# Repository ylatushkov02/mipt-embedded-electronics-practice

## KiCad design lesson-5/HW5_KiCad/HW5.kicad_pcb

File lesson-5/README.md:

# ДЗ № 5. Датчик протечки

## Задание
Нужно собрать датчик протечки со звуковой и световой индикацией:
- электроды — соединительные провода, испытание в стакане с водой;
- питание 5 В;
- сначала отладка на макетной плате, потом сборка на монтажной плате пайкой;
- электроды подключаются через винтовой клеммник.

Кроме того, нужны принципиальная схема в KiCad, разводка печатной платы, чертежи в PDF и скриншоты 3D-вида сверху и снизу.

## Схема
Ключ на одном NPN-транзисторе BC547B, включённом по схеме с общим эмиттером.
- Пока электроды сухие, R2 (100 кОм) держит базу на GND, и транзистор закрыт.
- Когда электроды в воде, ток течёт по цепи +5 В → вода → R1 (1 кОм) → база. Q1 открывается и одновременно включает:
  - активный зуммер TMB12A05;
  - светодиод D1 через R3 (220 Ом).

Расчёт:
- I_к ≈ 30 + 13 = 43 мА, это меньше 100 мА;
- I_б min ≈ 0,22 мА, поэтому сопротивление воды должно быть не больше ≈ 18 кОм;
- если электроды замкнуть накоротко, R1 ограничит ток базы до 4,3 мА.

## Файлы
| Файл | Что это |
|---|---|
| `HW5_KiCad/HW5.kicad_sch` | Принципиальная схема с расчётом, рамка ГОСТ (`GOST_A4.kicad_wks`) |
| `HW5_KiCad/HW5.kicad_pcb` | Печатная плата 60 × 35 мм: дорожки на B.Cu, винтовые клеммники J1 (питание) и J2 (электроды), размеры на User.Drawings, пояснения на User.Comments |
| `Схема_ДЗ5_предпросмотр.pdf` | Предпросмотр схемы |
| `Плата_ДЗ5_трассировка_предпросмотр.pdf` | Предпросмотр платы: трассировка и сборочный чертёж |
| `Монтажная_плата_схема_пайки.png` | Расположение элементов и перемычек на монтажной плате (шаг 2,54 мм) |
| `Макетка_датчик_протечки.png` | Сборка на макетной плате |
| `Видео_датчик_протечки_макетка.mov` | Испытание в стакане с водой (макетная плата) |

## Цепи
| Цепь | Выводы |
|---|---|
| +5V | J1.1, J2.2, BZ1.+, R3.1 |
| GND | J1.2, Q1.E, R2.2 |
| SENSE | J2.1, R1.1 |
| BASE | R1.2, R2.1, Q1.B |
| LOAD | Q1.C, BZ1.−, D1.K |
| LED_A | R3.2, D1.A |

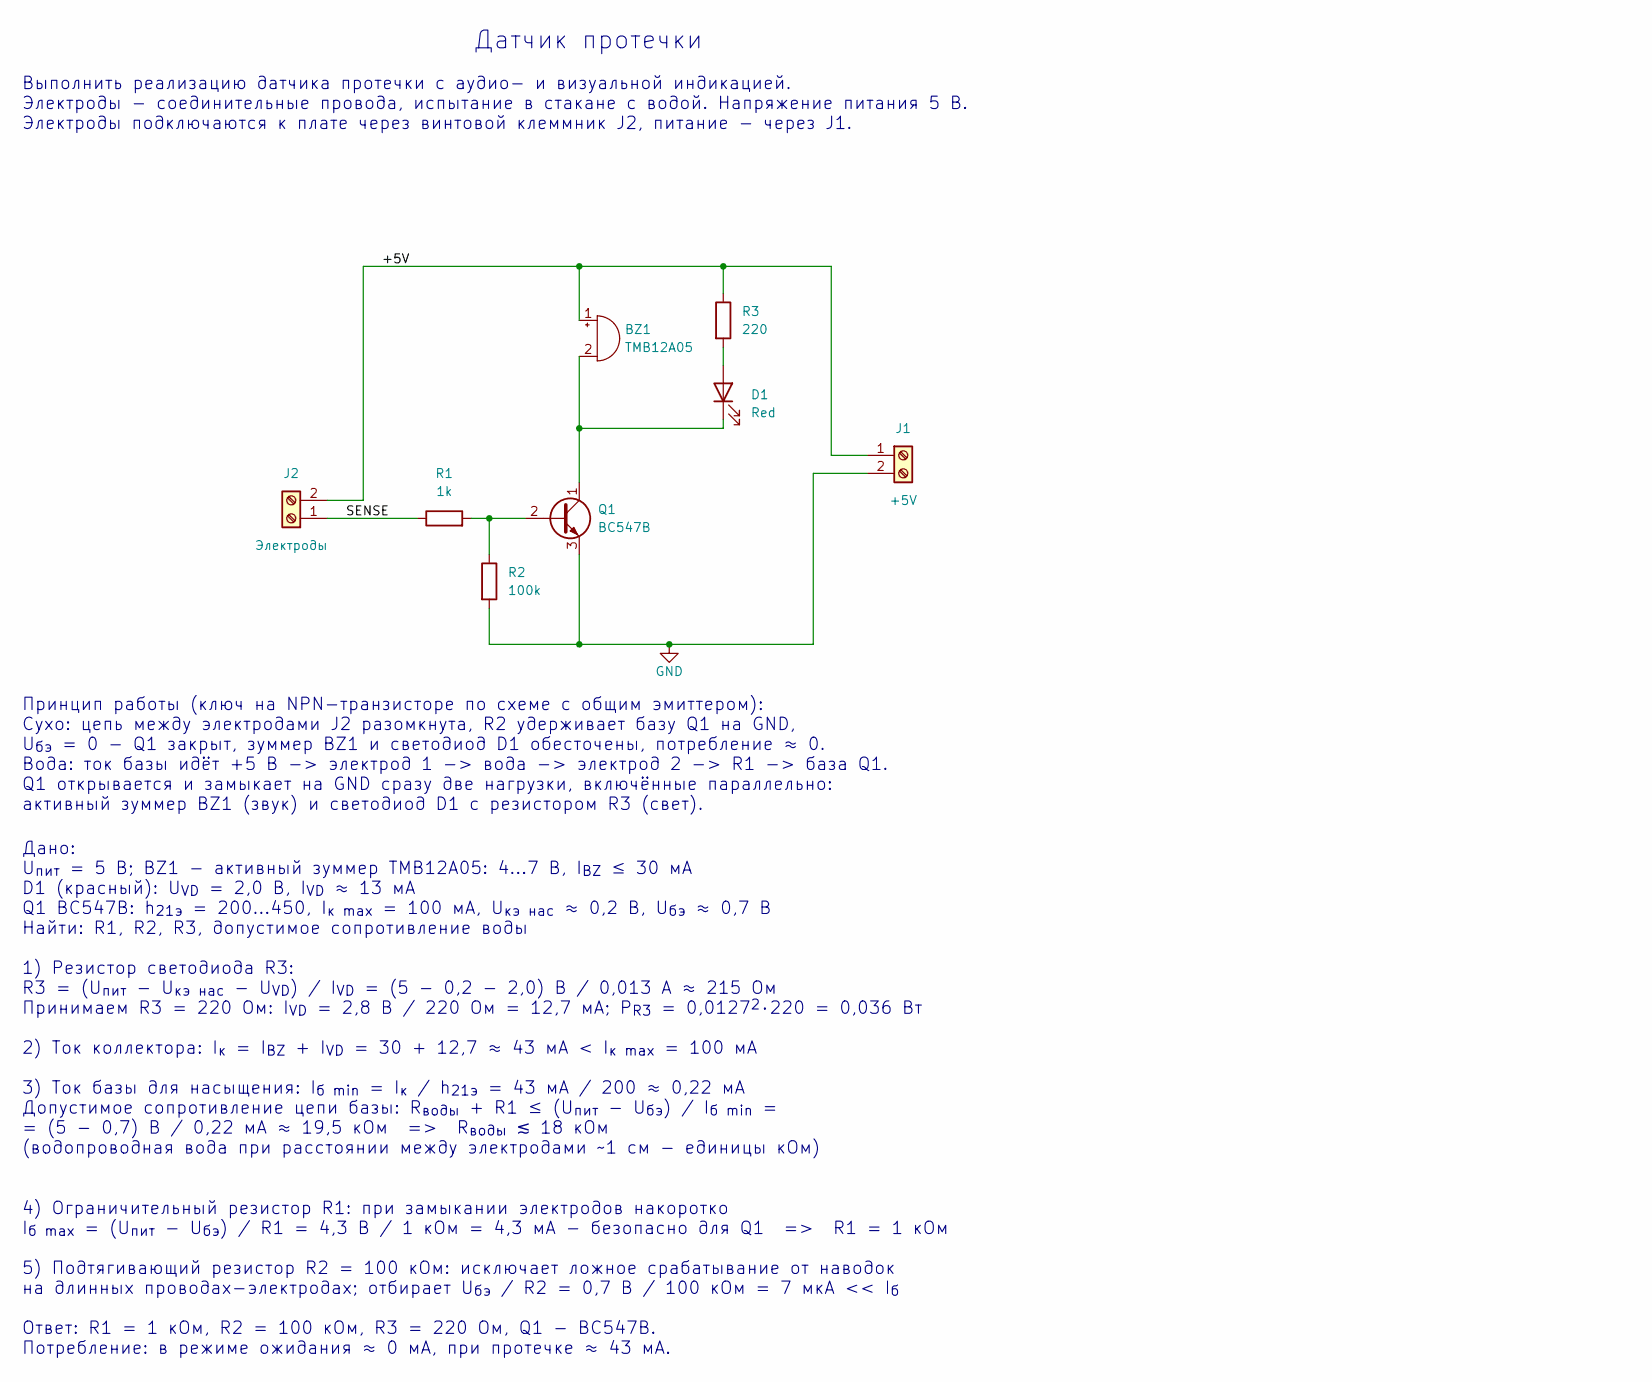
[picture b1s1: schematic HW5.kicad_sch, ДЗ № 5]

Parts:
BZ1: TMB12A05; Buzzer_12x9.5RM7.6
D1: Red; LED_D5.0mm
J1: +5V; TerminalBlock_MaiXu_MX126-5.0-02P_1x02_P5.00mm
J2: Электроды; TerminalBlock_MaiXu_MX126-5.0-02P_1x02_P5.00mm
Q1: BC547B; TO-92L_Inline
R1: 1k; R_Axial_DIN0207_L6.3mm_D2.5mm_P10.16mm_Horizontal
R2: 100k; R_Axial_DIN0207_L6.3mm_D2.5mm_P10.16mm_Horizontal
R3: 220; R_Axial_DIN0207_L6.3mm_D2.5mm_P10.16mm_Horizontal

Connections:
+5V: BZ1.1 (+), J1.1, J2.2, R3.1
BASE: Q1.2 (B), R1.2, R2.1
GND: J1.2, Q1.3 (E), R2.2
LED_A: D1.2 (A), R3.2
LOAD: BZ1.2 (-), D1.1 (K), Q1.1 (C)
SENSE: J2.1, R1.1

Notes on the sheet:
Датчик протечки
Выполнить реализацию датчика протечки с аудио- и визуальной индикацией. Электроды - соединительные провода, испытание в стакане с водой. Напряжение питания 5 В. Электроды подключаются к плате через винтовой клеммник J2, питание - через J1.
Принцип работы (ключ на NPN-транзисторе по схеме с общим эмиттером): Сухо: цепь между электродами J2 разомкнута, R2 удерживает базу Q1 на GND, U_{бэ} = 0 - Q1 закрыт, зуммер BZ1 и светодиод D1 обесточены, потребление ≈ 0. Вода: ток базы идёт +5 В -> электрод 1 -> вода -> электрод 2 -> R1 -> база Q1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
Дано: U_{пит} = 5 В; BZ1 - активный зуммер TMB12A05: 4...7 В, I_{BZ} ≤ 30 мА D1 (красный): U_{VD} = 2,0 В, I_{VD} ≈ 13 мА Q1 BC547B: h_{21э} = 200...450, I_{к max} = 100 мА, U_{кэ нас} ≈ 0,2 В, U_{бэ} ≈ 0,7 В Найти: R1, R2, R3, допустимое сопротивление воды 1) Резистор светодиода R3: R3 = (U_{пит} 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
4) Ограничительный резистор R1: при замыкании электродов накоротко I_{б max} = (U_{пит} - U_{бэ}) / R1 = 4,3 В / 1 кОм = 4,3 мА - безопасно для Q1 => R1 = 1 кОм 5) Подтягивающий резистор R2 = 100 кОм: исключает ложное срабатывание от наводок на длинных проводах-электродах; отбирает U_{бэ} / R2 = 0,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

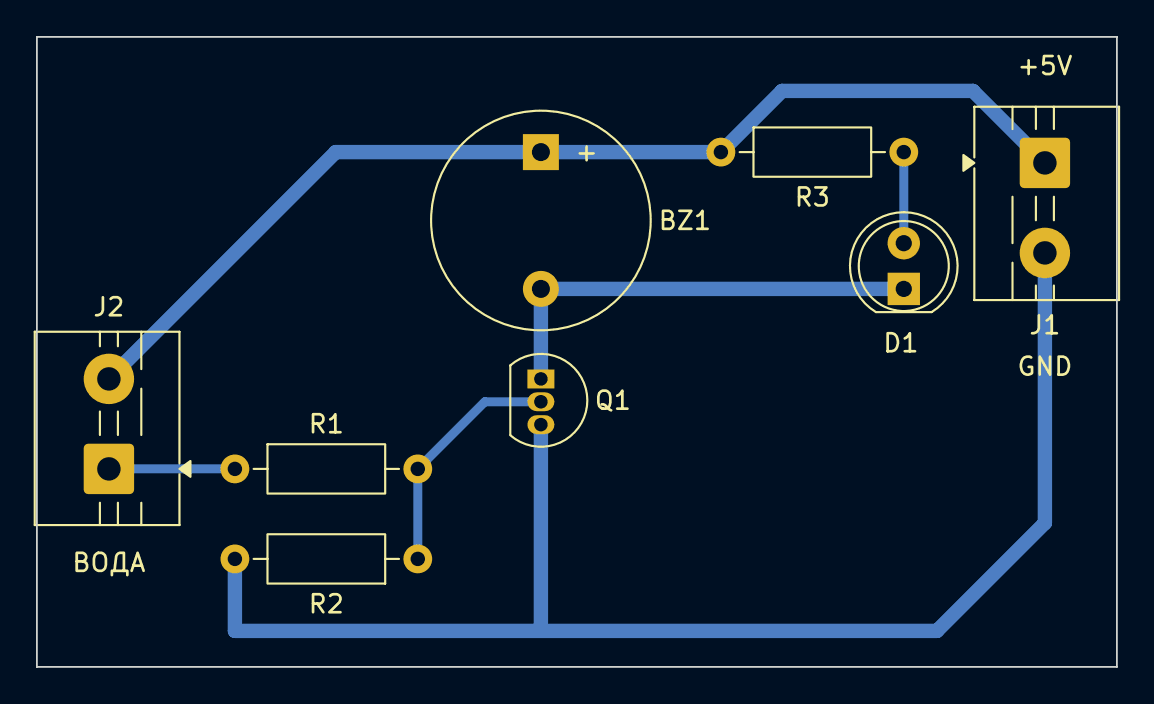
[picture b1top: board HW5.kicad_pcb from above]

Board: 2 copper layers, 60.0 x 35.0 mm, 8 parts (0 on the bottom side), 6 nets.

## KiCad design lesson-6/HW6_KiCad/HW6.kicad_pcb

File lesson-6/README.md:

# ДЗ № 6. Параметрический стабилизатор 12 В → 5 В

## Задание
Собрать на макетной плате параметрический стабилизатор: вход 12 В, выход 5 В.

Нагрузка — пять параллельных светодиодов:
- красный;
- жёлтый;
- зелёный;
- синий;
- белый.

В каждой ветви стоит свой резистор. Нужно рассчитать ток делителя со стабилитроном с учётом тока базы транзистора и запасом 30 %. Схему выполнить в KiCad. Дополнительно (задание со звёздочкой): развести плату.

Лампы накаливания в наборе нет, поэтому нагрузка состоит только из светодиодов.

## Схема
- Стабилитрон D1 BZX55C6V2 питается от 12 В через R1 = 1 кОм. Он задаёт опорное напряжение 6,2 В на базе Q1.
- Q1 (BC547B) включён эмиттерным повторителем, поэтому на выходе U = U_ст − U_бэ ≈ 6,2 − 0,75 = 5,45 В.
- R2 = 47 Ом в цепи коллектора забирает часть напряжения, поэтому транзистор греется меньше: 0,21 Вт вместо 0,34 Вт.

## Расчёт
- Резисторы светодиодов:
  - красный, жёлтый, зелёный (2,1 В): (5,45 − 2,1) / 10 мА ≈ 335 Ом, ставим **330 Ом**;
  - синий, белый (3,1 В): (5,45 − 3,1) / 10 мА ≈ 235 Ом, ставим **220 Ом**.
- Ток нагрузки: 3 · 10,2 + 2 · 10,7 ≈ 52 мА. С запасом 30 % — 68 мА.
- Ток базы: 68 мА / h21э (200) = **0,34 мА**.
- Ток делителя: I_б + I_ст min = 0,34 + 5 = 5,34 мА. Отсюда R1 = (12 − 6,2) / 5,34 мА ≈ 1,09 кОм, ставим **1 кОм**. Реальный ток делителя **5,8 мА**.
- Мощности:
  - транзистор: P_Q1 = 4,1 В · 52 мА = 0,21 Вт, это меньше 0,5 Вт;
  - стабилитрон: P_D1 = 36 мВт.

## Измерения
Мультиметр XL830L, лабораторный блок питания: 12,00 В, ограничение 0,15 А.

| Величина | Расчёт | Измерено | Отклонение |
|---|---|---|---|
| U_вых (шина +5 В — GND) | 5,45 В | **5,43 В** | −0,4 % |
| U_ст (база Q1 — GND) | 6,20 В | **6,18 В** | −0,3 % |
| U_R2 | 2,44 В | **2,56 В** | +5 % |
| Ток от БП | 58 мА | **61 мА** | +5 % |
| U_бэ = U_ст − U_вых | 0,75 В | 0,75 В | 0 % |

Что следует из измерений:
- Ток через R2 (нагрузка плюс база): 2,56 / 47 = 54,5 мА. По расчёту было 52 мА, светодиоды взяли чуть больше тока.
- Ток делителя: (12 − 6,18) / 1 кОм = 5,8 мА.
- Сумма 54,5 + 5,8 ≈ 60,3 мА сходится с показанием блока питания: 61 мА.
- Напряжение на транзисторе: U_кэ = 12 − 2,56 − 5,43 = 4,0 В. Мощность P_Q1 = 4,0 · 0,0545 ≈ 0,22 Вт, это меньше 0,5 Вт.
- Потребляемая мощность всей схемы — 0,73 Вт по показанию блока питания.

Вывод: выходное напряжение 5,43 В совпадает с расчётом с точностью до 0,5 %. Все пять светодиодов горят. Синий и белый светят ярче остальных: у них резисторы меньше (220 Ом), и они сами по себе эффективнее.

## Файлы
| Файл | Что это |
|---|---|
| `HW6_KiCad/HW6.kicad_sch` | Принципиальная схема с расчётом, рамка ГОСТ |
| `HW6_KiCad/HW6.kicad_pcb` | Плата 71 × 37 мм: дорожки на B.Cu, размеры на User.Drawings, пояснения на User.Comments |
| `Схема_ДЗ6_предпросмотр.pdf` | Схема (предпросмотр) |
| `Плата_ДЗ6_трассировка_предпросмотр.pdf` | Трассировка и сборочный чертёж |
| `Макетка_стабилизатор.png` | Схема сборки на макетной плате |
| `Фото_макетка_сборка.png`, `Фото_макетка_включена.png` | Собранная схема и она же во включённом состоянии |
| `Измерение_*.png` | Фото измерений: U_вых, U_ст, U_R2, ток от БП |

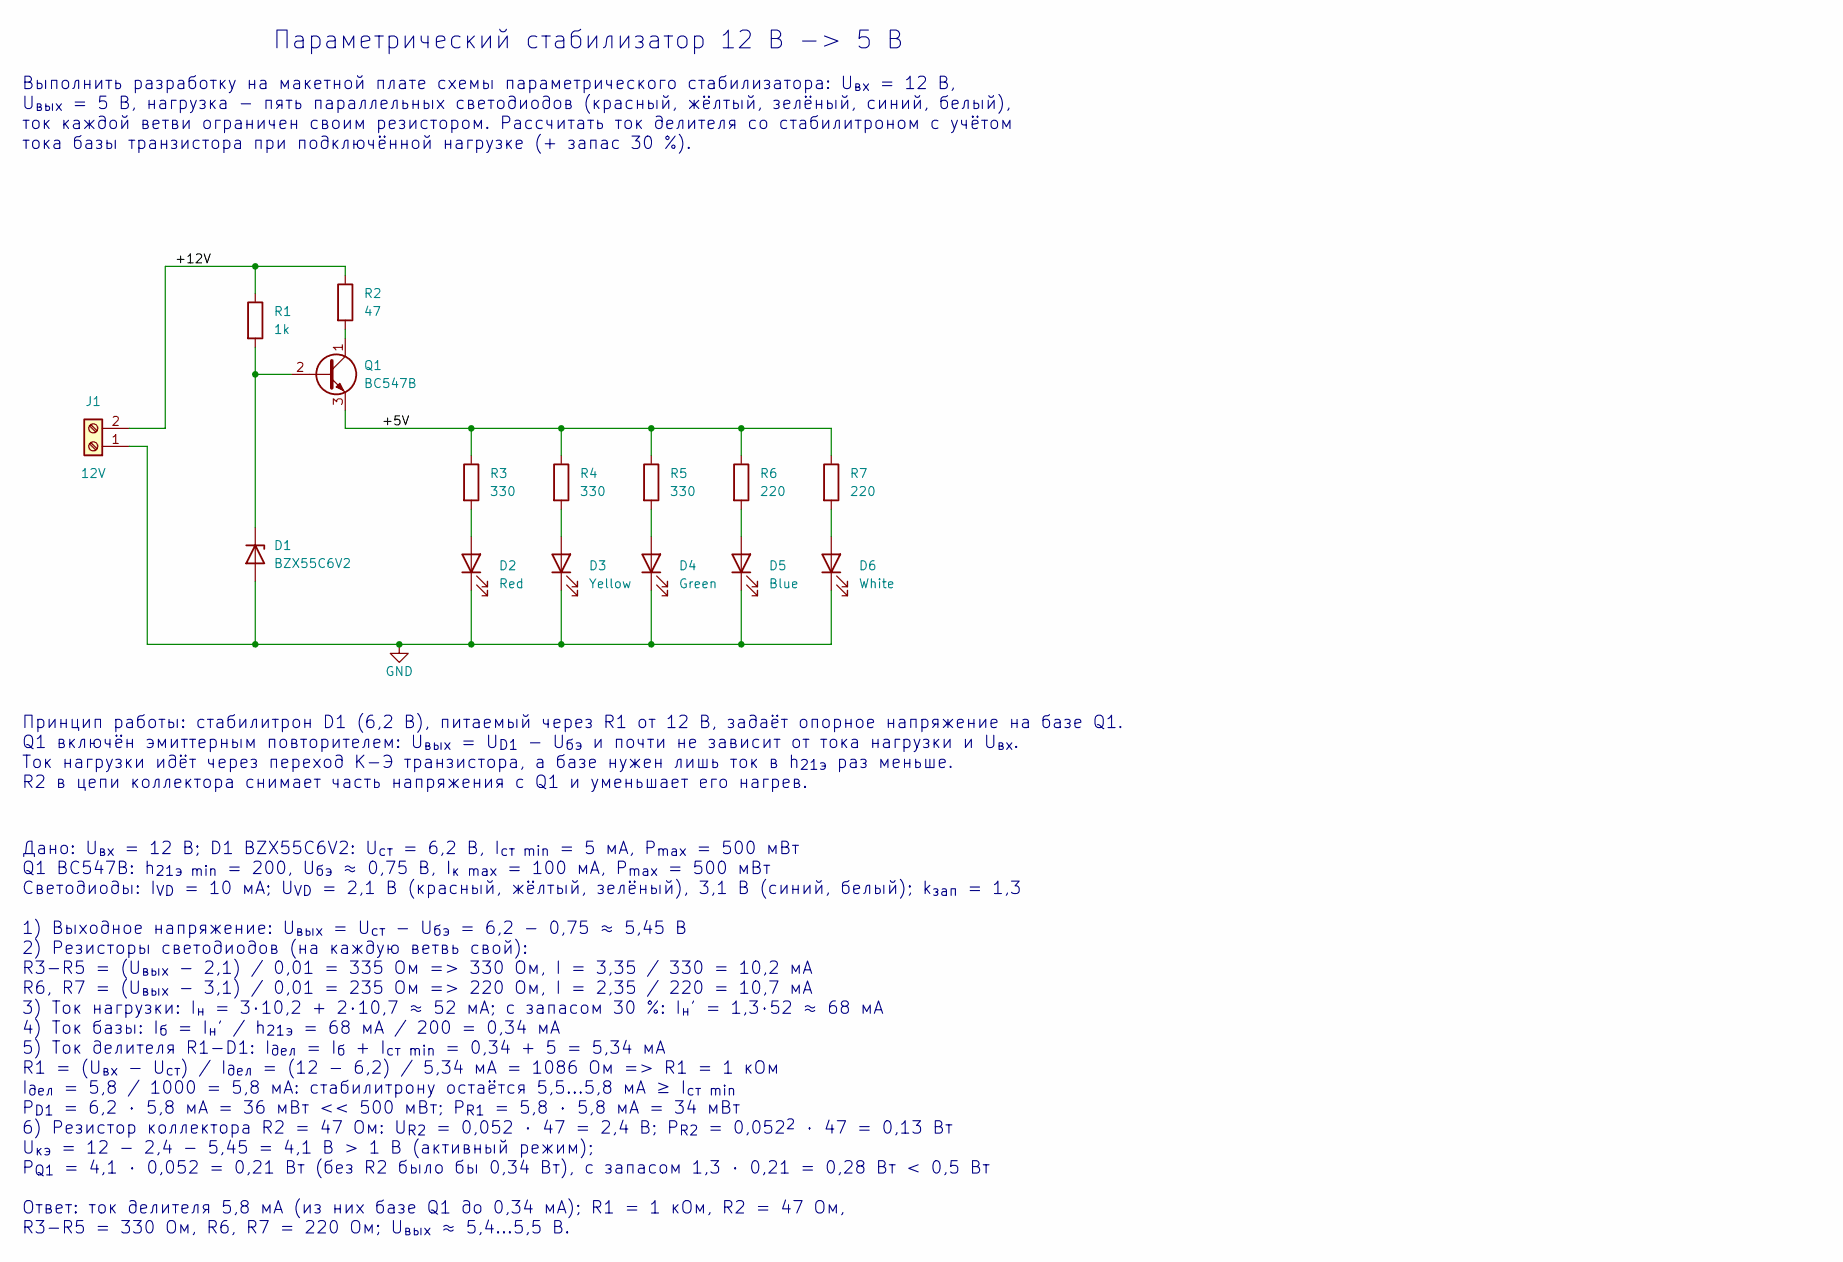
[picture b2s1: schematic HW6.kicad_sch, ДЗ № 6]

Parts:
D1: BZX55C6V2; D_DO-35_SOD27_P10.16mm_Horizontal
D2: Red; LED_D5.0mm
D3: Yellow; LED_D5.0mm
D4: Green; LED_D5.0mm
D5: Blue; LED_D5.0mm
D6: White; LED_D5.0mm
J1: 12V; TerminalBlock_MaiXu_MX126-5.0-02P_1x02_P5.00mm
Q1: BC547B; TO-92L_Inline
R1: 1k; R_Axial_DIN0207_L6.3mm_D2.5mm_P10.16mm_Horizontal
R2: 47; R_Axial_DIN0207_L6.3mm_D2.5mm_P10.16mm_Horizontal
R3, R4, R5: 330; R_Axial_DIN0207_L6.3mm_D2.5mm_P10.16mm_Horizontal
R6, R7: 220; R_Axial_DIN0207_L6.3mm_D2.5mm_P10.16mm_Horizontal

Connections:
+5V: Q1.3 (E), R3.1, R4.1, R5.1, R6.1, R7.1
+12V: J1.2, R1.1, R2.1
COL: Q1.1 (C), R2.2
GND: D1.2 (A), D2.1 (K), D3.1 (K), D4.1 (K), D5.1 (K), D6.1 (K), J1.1
LED1: D2.2 (A), R3.2
LED2: D3.2 (A), R4.2
LED3: D4.2 (A), R5.2
LED4: D5.2 (A), R6.2
LED5: D6.2 (A), R7.2
REF: D1.1 (K), Q1.2 (B), R1.2

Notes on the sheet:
Параметрический стабилизатор 12 В -> 5 В
Выполнить разработку на макетной плате схемы параметрического стабилизатора: U_{вх} = 12 В, U_{вых} = 5 В, нагрузка - пять параллельных светодиодов (красный, жёлтый, зелёный, синий, белый), ток каждой ветви ограничен своим резистором. Рассчитать ток делителя со стабилитроном с учётом тока базы тран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
Принцип работы: стабилитрон D1 (6,2 В), питаемый через R1 от 12 В, задаёт опорное напряжение на базе Q1. Q1 включён эмиттерным повторителем: U_{вых} = U_{D1} - U_{бэ} и почти не зависит от тока нагрузки и U_{вх}. Ток нагрузки идёт через переход К-Э транзистора, а базе нужен лишь ток в h_{21э} раз м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
Дано: U_{вх} = 12 В; D1 BZX55C6V2: U_{ст} = 6,2 В, I_{ст min} = 5 мА, P_{max} = 500 мВт Q1 BC547B: h_{21э min} = 200, U_{бэ} ≈ 0,75 В, I_{к max} = 100 мА, P_{max} = 500 мВт Светодиоды: I_{VD} = 10 мА; U_{VD} = 2,1 В (красный, жёлтый, зелёный), 3,1 В (синий, белый); k_{зап} = 1,3 1) Выходное напряже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

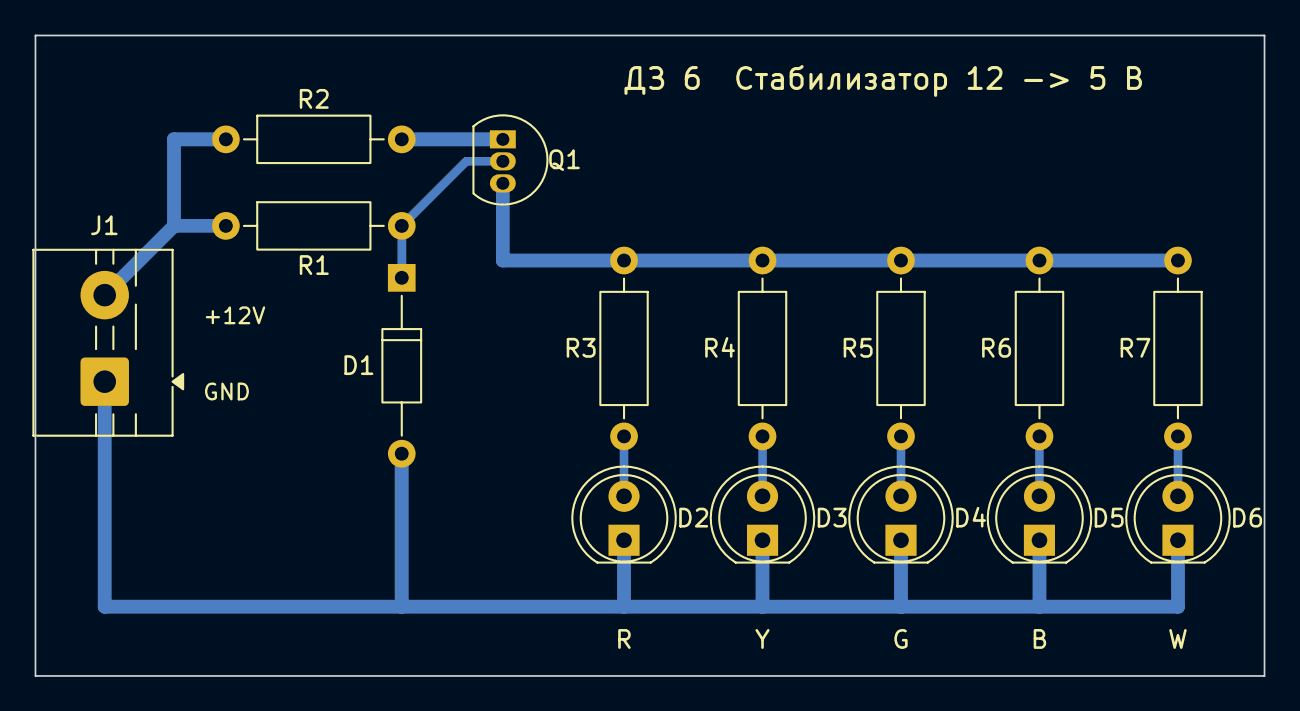
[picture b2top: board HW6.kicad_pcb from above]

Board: 2 copper layers, 71.0 x 37.0 mm, 15 parts (0 on the bottom side), 10 nets.

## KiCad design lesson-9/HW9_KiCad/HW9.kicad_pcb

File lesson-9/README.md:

# ДЗ № 9. Включение генератора одной кнопкой: два таймера NE555, питание 9 В от LM317

## Задание
1. Сделать цепь питания 9 В от входных 12 В на линейном стабилизаторе LM317T.
2. На NE555 в бистабильном режиме сделать включение и выключение нагрузки одной тактовой кнопкой: первое нажатие включает, повторное выключает.
3. На NE555 в астабильном режиме сделать генератор импульсов 1…10 Гц со светодиодом.
4. Генератор из п. 3 считать нагрузкой для п. 2 и подавать на него питание через транзисторный ключ, а не напрямую с вывода 3.

Сборка на макетной плате, этапы работы снять на видео. Принципиальная схема в KiCad, описание и чертёж в PDF. Задание со звёздочкой: развести плату, приложить PDF трассировки и 3D-вид сверху и снизу.

## Схема
- **Питание.** U1 LM317T с делителем R1 330 Ом и R2 + R3 (2 × 1 кОм) даёт 8,9 В на шине +9V. C1 0,1 мкФ и C2 10 мкФ — фильтры. Красный D1 с R4 1 кОм показывает, что +9 В есть.
- **Триггер U2 (NE555, бистабильный режим).**
  - Выводы 2 (TRIG) и 6 (THRES) соединены. Делитель R5–R6 (10 кОм + 10 кОм) держит их на 4,5 В, то есть между порогами 3 В и 6 В, поэтому выход хранит своё состояние.
  - Конденсатор C3 10 мкФ через R7 100 кОм заряжается до уровня выхода.
  - Кнопка SW1 подключает C3 к выводам 2 и 6. Если выход выключен, на C3 около 0 В: срабатывает TRIG, и выход включается. Если выход включён, на C3 около 7,5 В: срабатывает THRES, и выход выключается.
  - R8 10 кОм и C4 10 мкФ держат вход сброса (вывод 4) в нуле первые 0,1 с после подачи питания. Поэтому U2 всегда стартует с выключенной нагрузкой.
- **Ключ Q1 (BC547B, эмиттерный повторитель).** Выход U2 через R10 1 кОм идёт на базу, коллектор на +9V. С эмиттера снимается питание нагрузки +VG ≈ 6,7 В. Жёлтый D2 с R9 1 кОм горит, пока нагрузка включена.
- **Генератор U3 (NE555, астабильный режим).** R11 и R12 по 10 кОм и C6 10 мкФ задают частоту 4,8 Гц. Зелёный D3 с R13 330 Ом мигает.
- **C5, C7 0,1 мкФ** — фильтры на выводах CONT (5) обоих таймеров.

## Расчёт
| Величина | Расчёт | Значение |
|---|---|---|
| Выход LM317 | 1,25 · (1 + 2000/330) + 50 мкА · 2 кОм | **8,93 В** |
| Ток делителя R1 | 1,25 / 330 | 3,8 мА ≥ 3,5 мА (минимальная нагрузка LM317) |
| Пороги U2 | 9/3 и 2·9/3 | 3 В и 6 В; делитель R5–R6 даёт 4,5 В |
| Напряжение при удержании кнопки | 4,5 · 100/105 + U<sub>вых</sub> · 5/105 | 4,29 В (выкл.) / 4,64 В (вкл.): между порогами, повторного переключения нет |
| Постоянная C3 | R7 · C3 = 100 кОм · 10 мкФ | 1 с; пауза между нажатиями ≥ 0,7 с |
| Сброс при включении | R8 · C4 = 10 кОм · 10 мкФ | 0,1 с |
| Ток нагрузки ключа | ≈ 4 (U3) + 9,7 (D3) + 4,7 (D2) | ≈ 19 мА, ток базы ≈ 0,1 мА |
| +VG | 7,5 − 0,1 · 1 − 0,7 | **≈ 6,7 В** |
| Мощность Q1 | (8,9 − 6,7) · 19 мА | 42 мВт (допустимо 500 мВт) |
| Частота U3 | 1,44 / ((R11 + 2·R12) · C6) = 1,44 / (30 кОм · 10 мкФ) | **4,8 Гц** (в пределах 1…10 Гц) |
| Импульс / пауза | 0,693 · 20 кОм · 10 мкФ / 0,693 · 10 кОм · 10 мкФ | 0,139 с / 0,069 с |
| R13 (D3) | (6,7 − 1,5 − 2) / 10 мА | 320 Ом → **330 Ом** |
| R4, R9 | (8,9 − 2) / 1 кОм; (6,7 − 2) / 1 кОм | 6,9 мА; 4,7 мА |
| Мощность LM317 | (12 − 8,9) · 35 мА | 0,11 Вт, радиатор не нужен |

## Сборка и проверка на макетке
Раскладка по шагам — `Макетка_NE555_триггер_генератор.png`.
- **Верхние шины:** внешняя +9 В, внутренняя GND.
- **Нижние шины:** внутренняя GND, внешняя +VG (питание генератора).
- **Подключение 12 В:** провод с +12 В от лабораторного блока питания идёт прямо на вход LM317 (отверстие j5).

Порядок съёмки видео:
1. Подать питание 12 В: горит только красный D1.
2. Нажать SW1: загорается жёлтый D2, зелёный D3 мигает примерно 5 раз в секунду.
3. Нажать SW1 ещё раз: D2 и D3 гаснут.

Между нажатиями делать паузу не меньше секунды. Мультиметром удобно показать 8,9 В на верхней шине и +VG ≈ 6,7 В / 0 В на нижней внешней шине.

## Файлы
| Файл | Что это |
|---|---|
| `HW9_KiCad/HW9.kicad_sch` | Принципиальная схема с расчётом, рамка ГОСТ |
| `HW9_KiCad/HW9.kicad_pcb` | Двусторонняя плата 72 × 76 мм: дорожки на двух слоях, размеры на User.Drawings, пояснения на User.Comments |
| `Схема_ДЗ9_предпросмотр.pdf` | Схема в PDF |
| `Плата_ДЗ9_трассировка_предпросмотр.pdf` | Трассировка и сборочный чертёж |
| `Макетка_NE555_триггер_генератор.png` | Сборка на макетной плате по шагам |

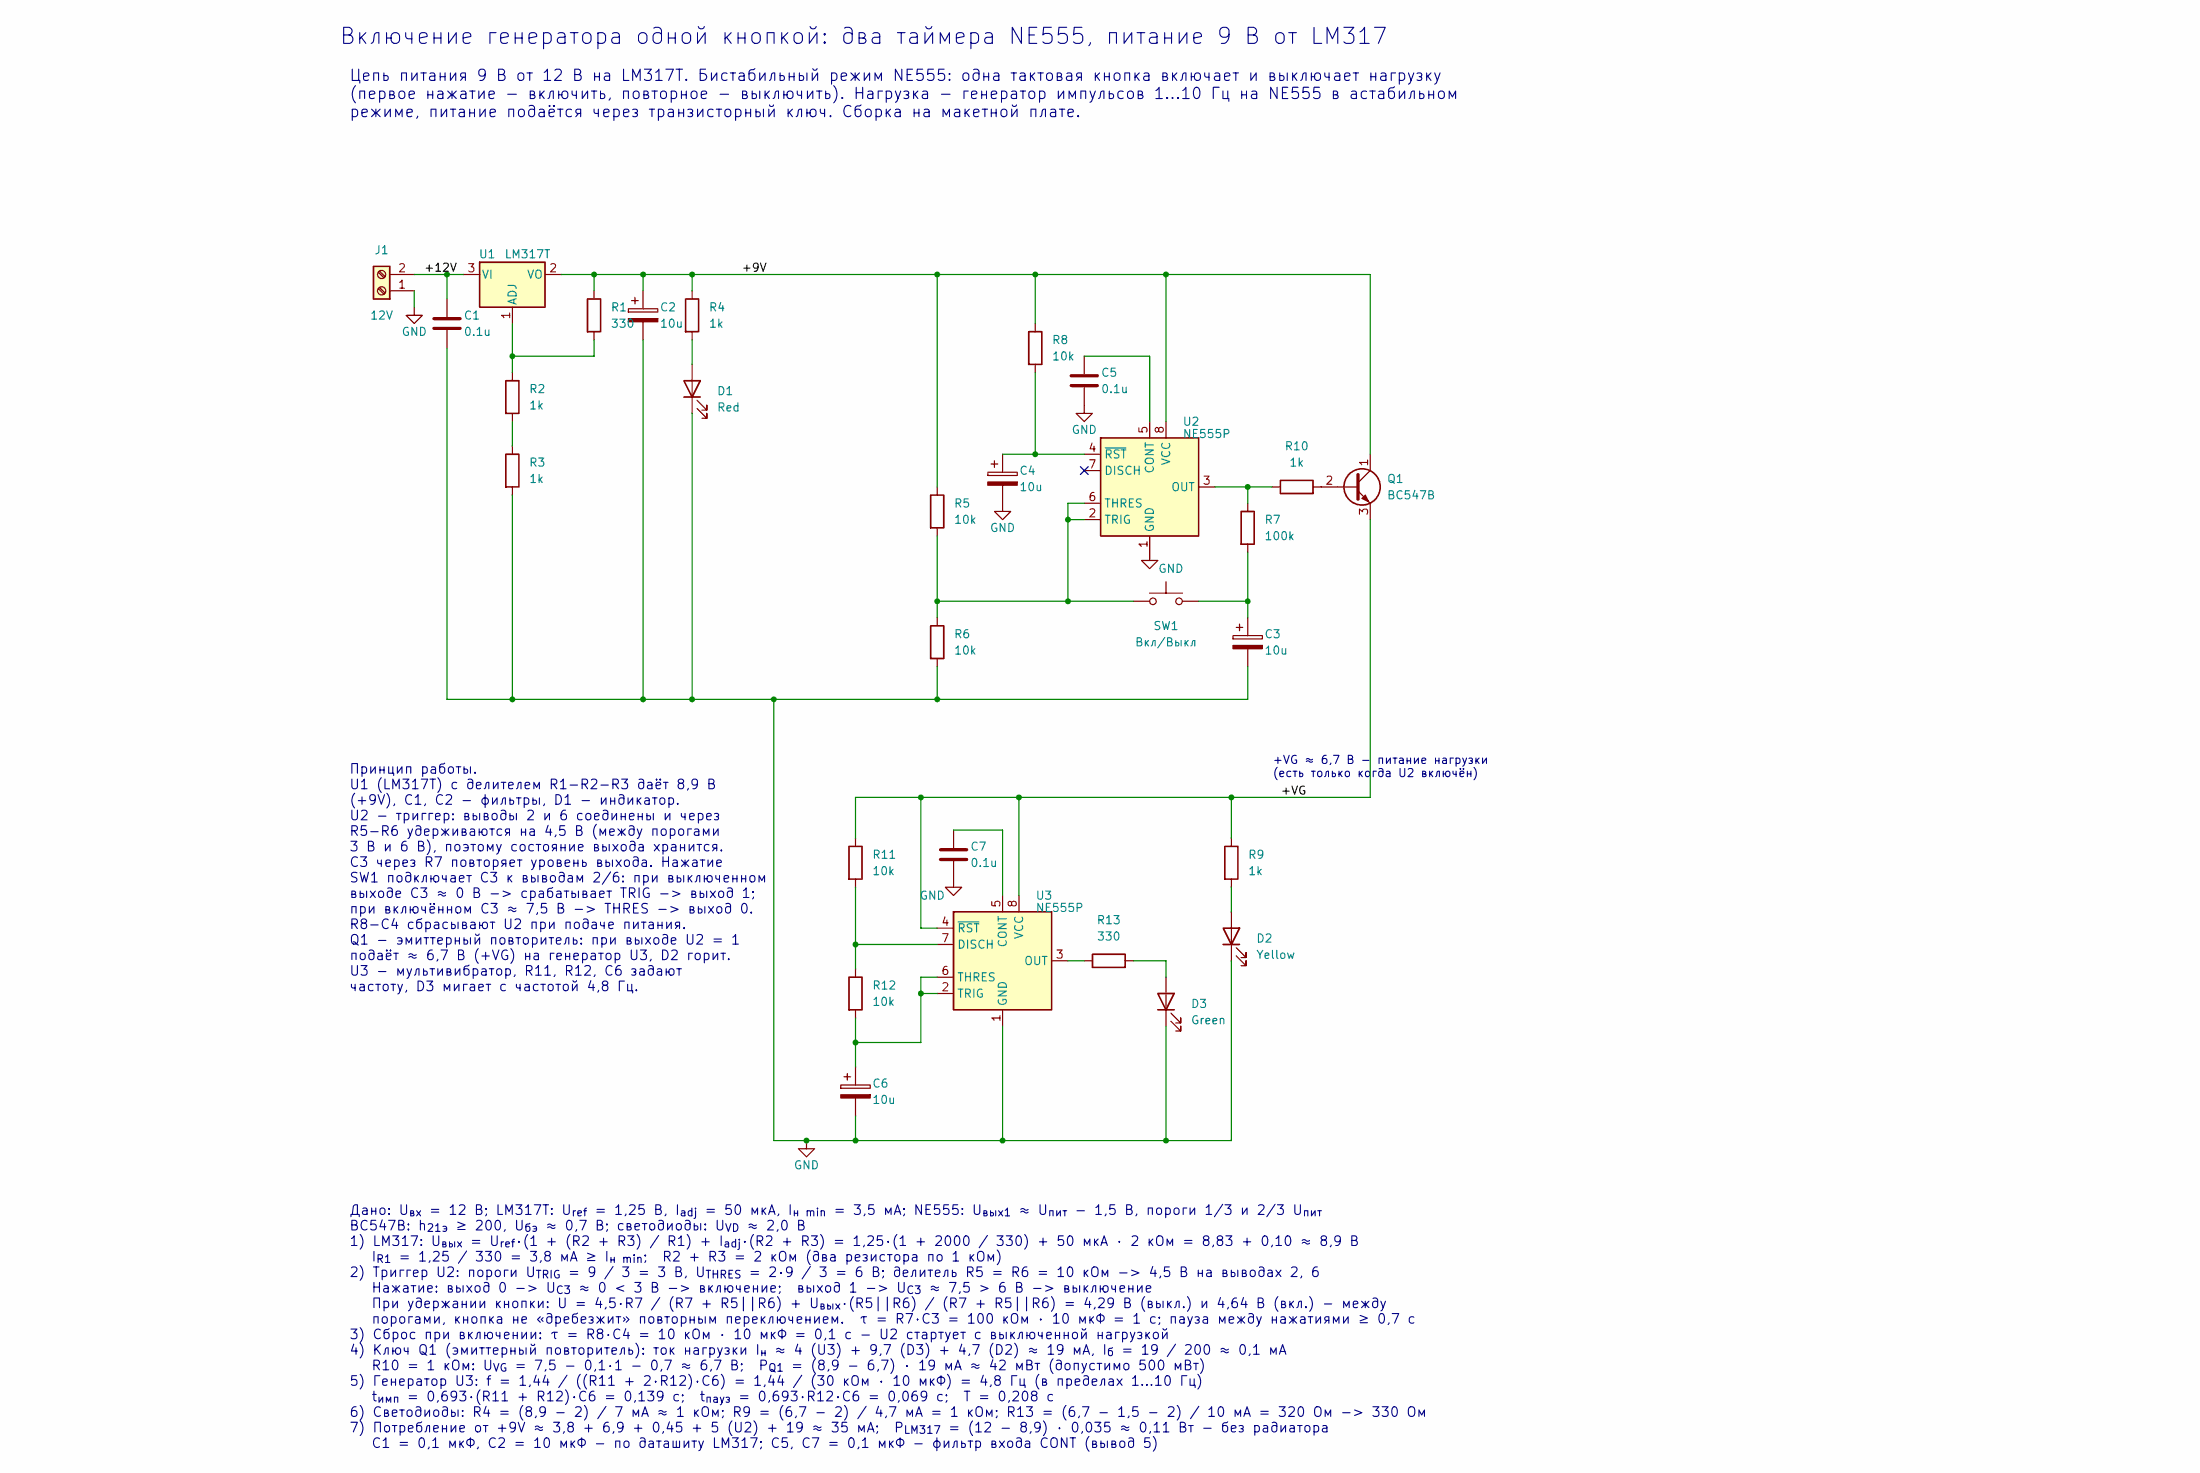
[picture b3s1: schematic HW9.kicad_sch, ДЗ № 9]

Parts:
C1, C5, C7: 0.1u; C_Disc_D5.0mm_W2.5mm_P5.00mm
C2, C3, C4, C6: 10u; CP_Radial_D5.0mm_P2.00mm
D1: Red; LED_D5.0mm
D2: Yellow; LED_D5.0mm
D3: Green; LED_D5.0mm
J1: 12V; TerminalBlock_MaiXu_MX126-5.0-02P_1x02_P5.00mm
Q1: BC547B; TO-92L_Inline
R1, R13: 330; R_Axial_DIN0207_L6.3mm_D2.5mm_P10.16mm_Horizontal
R2, R3, R4, R9, R10: 1k; R_Axial_DIN0207_L6.3mm_D2.5mm_P10.16mm_Horizontal
R5, R6, R8, R11, R12: 10k; R_Axial_DIN0207_L6.3mm_D2.5mm_P10.16mm_Horizontal
R7: 100k; R_Axial_DIN0207_L6.3mm_D2.5mm_P10.16mm_Horizontal
SW1: Вкл/Выкл; SW_PUSH_6mm
U1: LM317T; TO-220-3_Vertical
U2, U3: NE555P; DIP-8_W7.62mm

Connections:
+9V: C2.1, Q1.1 (C), R1.1, R4.1, R5.1, R8.1, U1.2 (VO), U2.8 (VCC)
+12V: C1.1, J1.2, U1.3 (VI)
A23: R2.2, R3.1
ADJ: R1.2, R2.1, U1.1 (ADJ)
B: Q1.2 (B), R10.2
CT: C3.1, R7.2, SW1.2
CV2: C5.1, U2.5 (CONT)
CV3: C7.1, U3.5 (CONT)
DIS: R11.2, R12.1, U3.7 (DISCH)
GND: C1.2, C2.2, C3.2, C4.2, C5.2, C6.2, C7.2, D1.1 (K), D2.1 (K), D3.1 (K), J1.1, R3.2, R6.2, U2.1 (GND), U3.1 (GND)
LED2A: D2.2 (A), R9.2
LED3A: D3.2 (A), R13.2
NODE: R5.2, R6.1, SW1.1, U2.2 (TRIG), U2.6 (THRES)
OUT2: R7.1, R10.1, U2.3 (OUT)
OUT3: R13.1, U3.3 (OUT)
PLED: D1.2 (A), R4.2
RST2: C4.1, R8.2, U2.4 (~RST)
TH3: C6.1, R12.2, U3.2 (TRIG), U3.6 (THRES)
VG: Q1.3 (E), R9.1, R11.1, U3.4 (~RST), U3.8 (VCC)

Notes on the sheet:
Включение генератора одной кнопкой: два таймера NE555, питание 9 В от LM317
Цепь питания 9 В от 12 В на LM317T. Бистабильный режим NE555: одна тактовая кнопка включает и выключает нагрузку (первое нажатие - включить, повторное - выключить). Нагрузка - генератор импульсов 1...10 Гц на NE555 в астабильном режиме, питание подаётся через транзисторный ключ. Сборка на макетной 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
+VG ≈ 6,7 В - питание нагрузки (есть только когда U2 включён)
Принцип работы. U1 (LM317T) с делителем R1-R2-R3 даёт 8,9 В (+9V), C1, C2 - фильтры, D1 - индикатор. U2 - триггер: выводы 2 и 6 соединены и через R5-R6 удерживаются на 4,5 В (между порогами 3 В и 6 В), поэтому состояние выхода хранится. C3 через R7 повторяет уровень выхода. Нажатие SW1 подключает C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
Дано: U_{вх} = 12 В; LM317T: U_{ref} = 1,25 В, I_{adj} = 50 мкА, I_{н min} = 3,5 мА; NE555: U_{вых1} ≈ U_{пит} - 1,5 В, пороги 1/3 и 2/3 U_{пит} BC547B: h_{21э} ≥ 200, U_{бэ} ≈ 0,7 В; светодиоды: U_{VD} ≈ 2,0 В 1) LM317: U_{вых} = U_{ref}·(1 + (R2 + R3) / R1) + I_{adj}·(R2 + R3) = 1,25·(1 + 2000 / 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

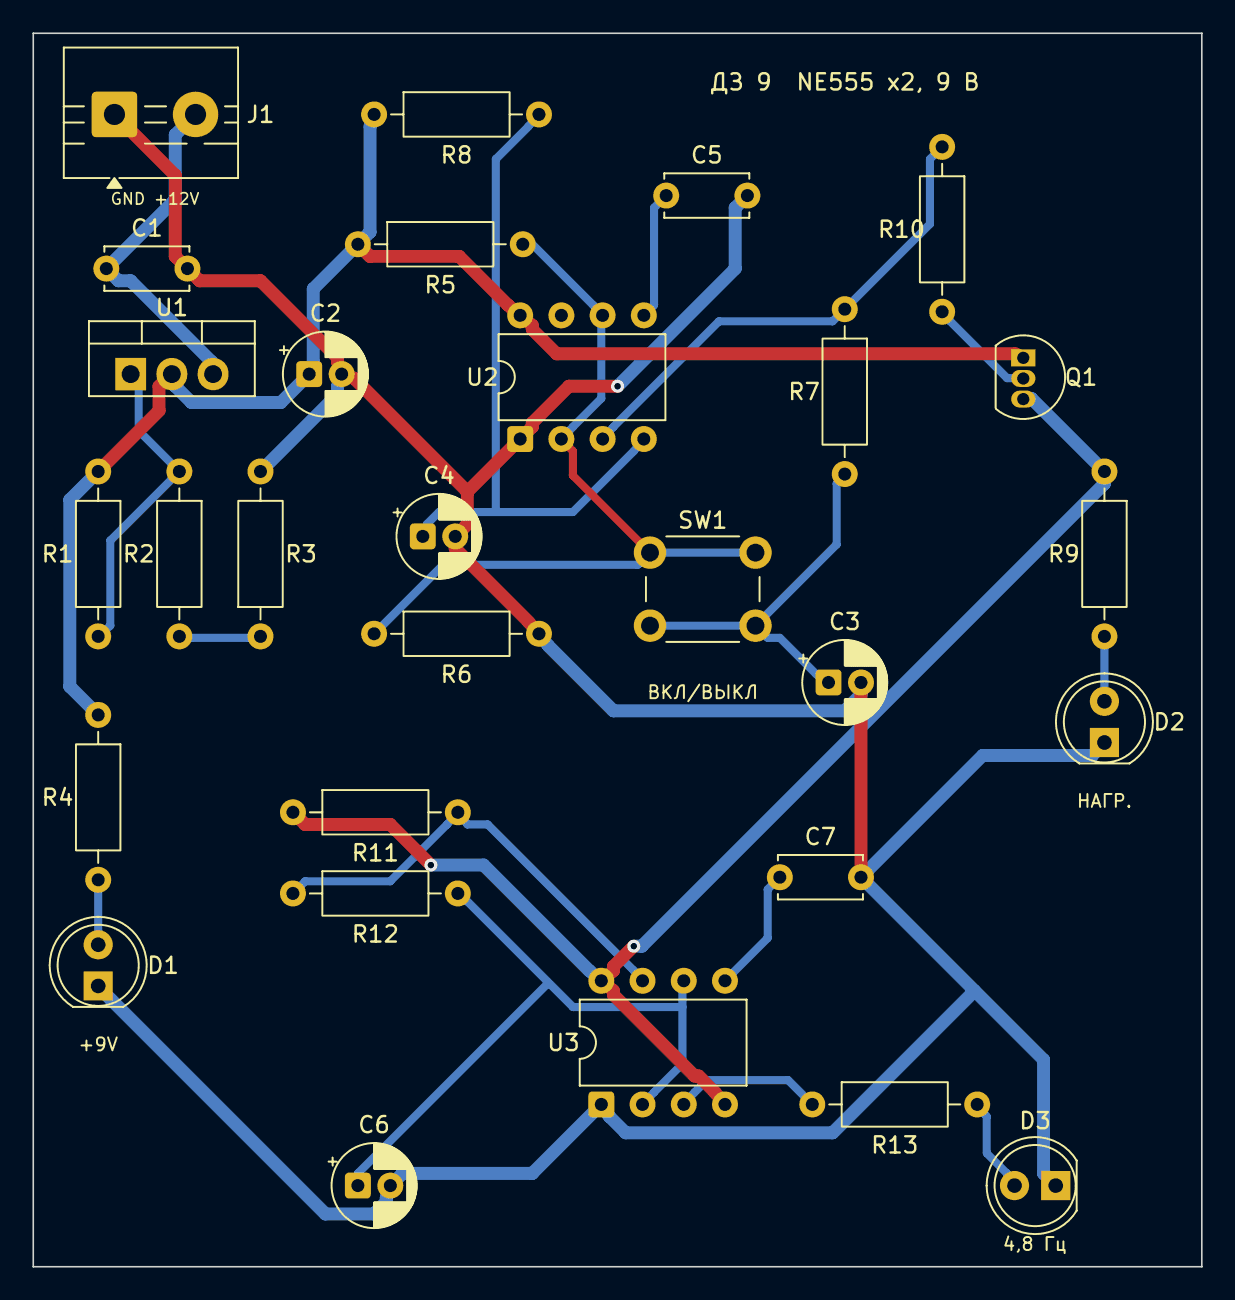
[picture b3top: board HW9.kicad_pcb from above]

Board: 2 copper layers, 72.0 x 76.0 mm, 29 parts (0 on the bottom side), 19 nets.

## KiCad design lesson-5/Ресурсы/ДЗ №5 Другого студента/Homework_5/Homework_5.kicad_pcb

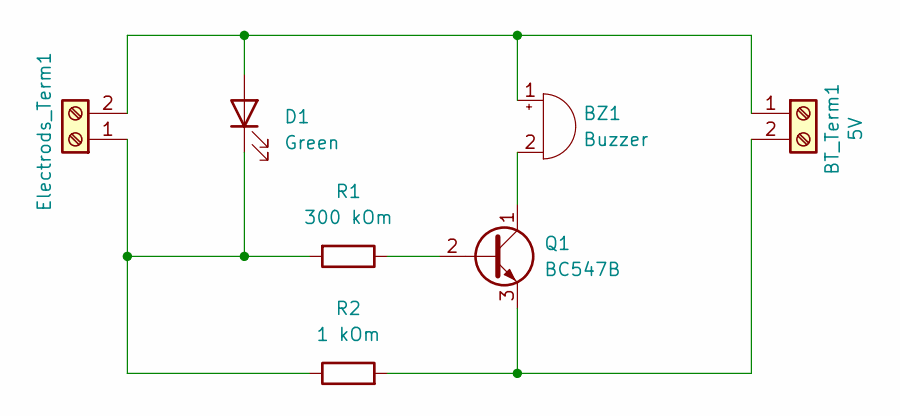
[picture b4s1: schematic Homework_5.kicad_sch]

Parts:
BT_Term1: 5V; TerminalBlock_MaiXu_MX126-5.0-02P_1x02_P5.00mm
BZ1: Buzzer; Buzzer_12x9.5RM7.6
D1: Green; LED_D5.0mm
Electrods_Term1: TerminalBlock_MaiXu_MX126-5.0-02P_1x02_P5.00mm
Q1: BC547B; TO-92L_Inline
R1: 300 kOm; R_Axial_DIN0207_L6.3mm_D2.5mm_P10.16mm_Horizontal
R2: 1 kOm; R_Axial_DIN0207_L6.3mm_D2.5mm_P10.16mm_Horizontal

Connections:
unnamed: BT_Term1.1, BZ1.1 (+), D1.2 (A), Electrods_Term1.2
unnamed: BT_Term1.2, Q1.3 (E), R2.2
unnamed: BZ1.2 (-), Q1.1 (C)
unnamed: D1.1 (K), Electrods_Term1.1, R1.2, R2.1
unnamed: Q1.2 (B), R1.1

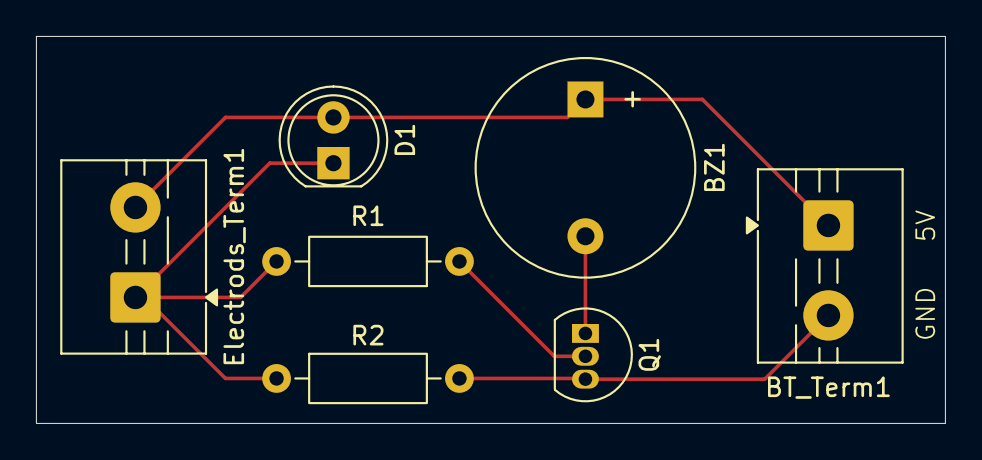
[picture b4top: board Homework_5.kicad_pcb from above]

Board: 2 copper layers, 50.5 x 21.5 mm, 7 parts (0 on the bottom side), 5 nets.

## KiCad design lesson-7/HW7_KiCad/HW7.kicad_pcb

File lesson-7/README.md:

# ДЗ № 7. Управление реле 5 В от кнопки через оптопару

## Задание
Нужно собрать на макетной плате схему управления реле 5 В от тактовой кнопки через оптопару, питающуюся от 3,3 В:
- предусмотреть визуальную индикацию состояния реле;
- питание 5 В и 3,3 В брать с модуля питания макетной платы;
- между управляющим сигналом и реле должна быть опторазвязка (общий минус питаний допускается);
- рекомендуется добавить транзистор.

Дополнительно (задание со звёздочкой): выполнить схему и разводку платы в KiCad и приложить PDF и 3D-вид.

## Схема
- **Цепь 3,3 В:** кнопка SW1 → R1 220 Ом → светодиод оптопары U1 (UMW817B — аналог PC817, группа B, CTR 130–260 %) → GND.
- **Цепь 5 В:**
  - фототранзистор U1 → R2 1 кОм → база Q1 (BC547B);
  - R3 10 кОм подтягивает базу к GND;
  - Q1 включает обмотку реле K1 (SRD-05VDC / T73);
  - D1 (1N4007) гасит выброс ЭДС самоиндукции обмотки.
- **Индикация:** контакт реле COM–NO подаёт +5 В через R4 330 Ом на зелёный светодиод D2. Светодиод горит только тогда, когда контакт действительно замкнулся.

Цепи 3,3 В и 5 В связаны только светом внутри оптопары. Общий минус у них, как и разрешено в задании.

## Расчёт
| Величина | Формула | Значение |
|---|---|---|
| Ток обмотки (R = 55 Ом, худший случай) | 5 / 55 | 91 мА (< 100 мА у BC547) |
| Ток базы (k = 4, h21э = 100) | 4 · 91 / 100 | 3,6 мА |
| R2 | (5 − 0,2 − 0,9) / 3,6 мА | 1083 Ом → **1 кОм** (I_б = 3,9 мА) |
| Ток светодиода оптопары | I_б / CTR_min = 3,9 / 1,3 | ≥ 3 мА → берём 10 мА с запасом |
| R1 | (3,3 − 1,2) / 10 мА | 210 Ом → **220 Ом** (I_F = 9,5 мА) |
| R3 | подтяжка базы к GND | **10 кОм** (отбирает 0,09 мА) |
| R4 | (5 − 2,2) / 10 мА | 280 Ом → **330 Ом** (8,5 мА) |
| Мощность Q1 | 0,2 В · 91 мА | 18 мВт |

## Результат
Схема собрана на макетной плате и работает:
- **кнопка отпущена:** реле отпущено, светодиод D2 не горит;
- **кнопка нажата:** реле щёлкает, контакт COM–NO замыкается, светодиод D2 горит зелёным.

Реле T73 установлено обмоткой вверх, так что все пять ножек попадают в отверстия. COM подключён к шине +5 В перемычкой.

## Файлы
| Файл | Что это |
|---|---|
| `HW7_KiCad/HW7.kicad_sch` | Принципиальная схема с расчётом, рамка ГОСТ |
| `HW7_KiCad/HW7.kicad_pcb` | Плата 86 × 49 мм: дорожки B.Cu и перемычка +5V на F.Cu, размеры на User.Drawings, пояснения на User.Comments |
| `Схема_ДЗ7_предпросмотр.pdf` | Предпросмотр схемы |
| `Плата_ДЗ7_трассировка_предпросмотр.pdf` | Трассировка и сборочный чертёж |
| `Макетка_реле_оптопара.png` | Как собрать на макетной плате |
| `Фото_макетка_кнопка_отпущена.png`, `Фото_макетка_кнопка_нажата.png` | Собранная схема в обоих состояниях |
| `Видео_реле_оптопара.mov` | Работа схемы: нажатие кнопки, щелчок реле, светодиод |

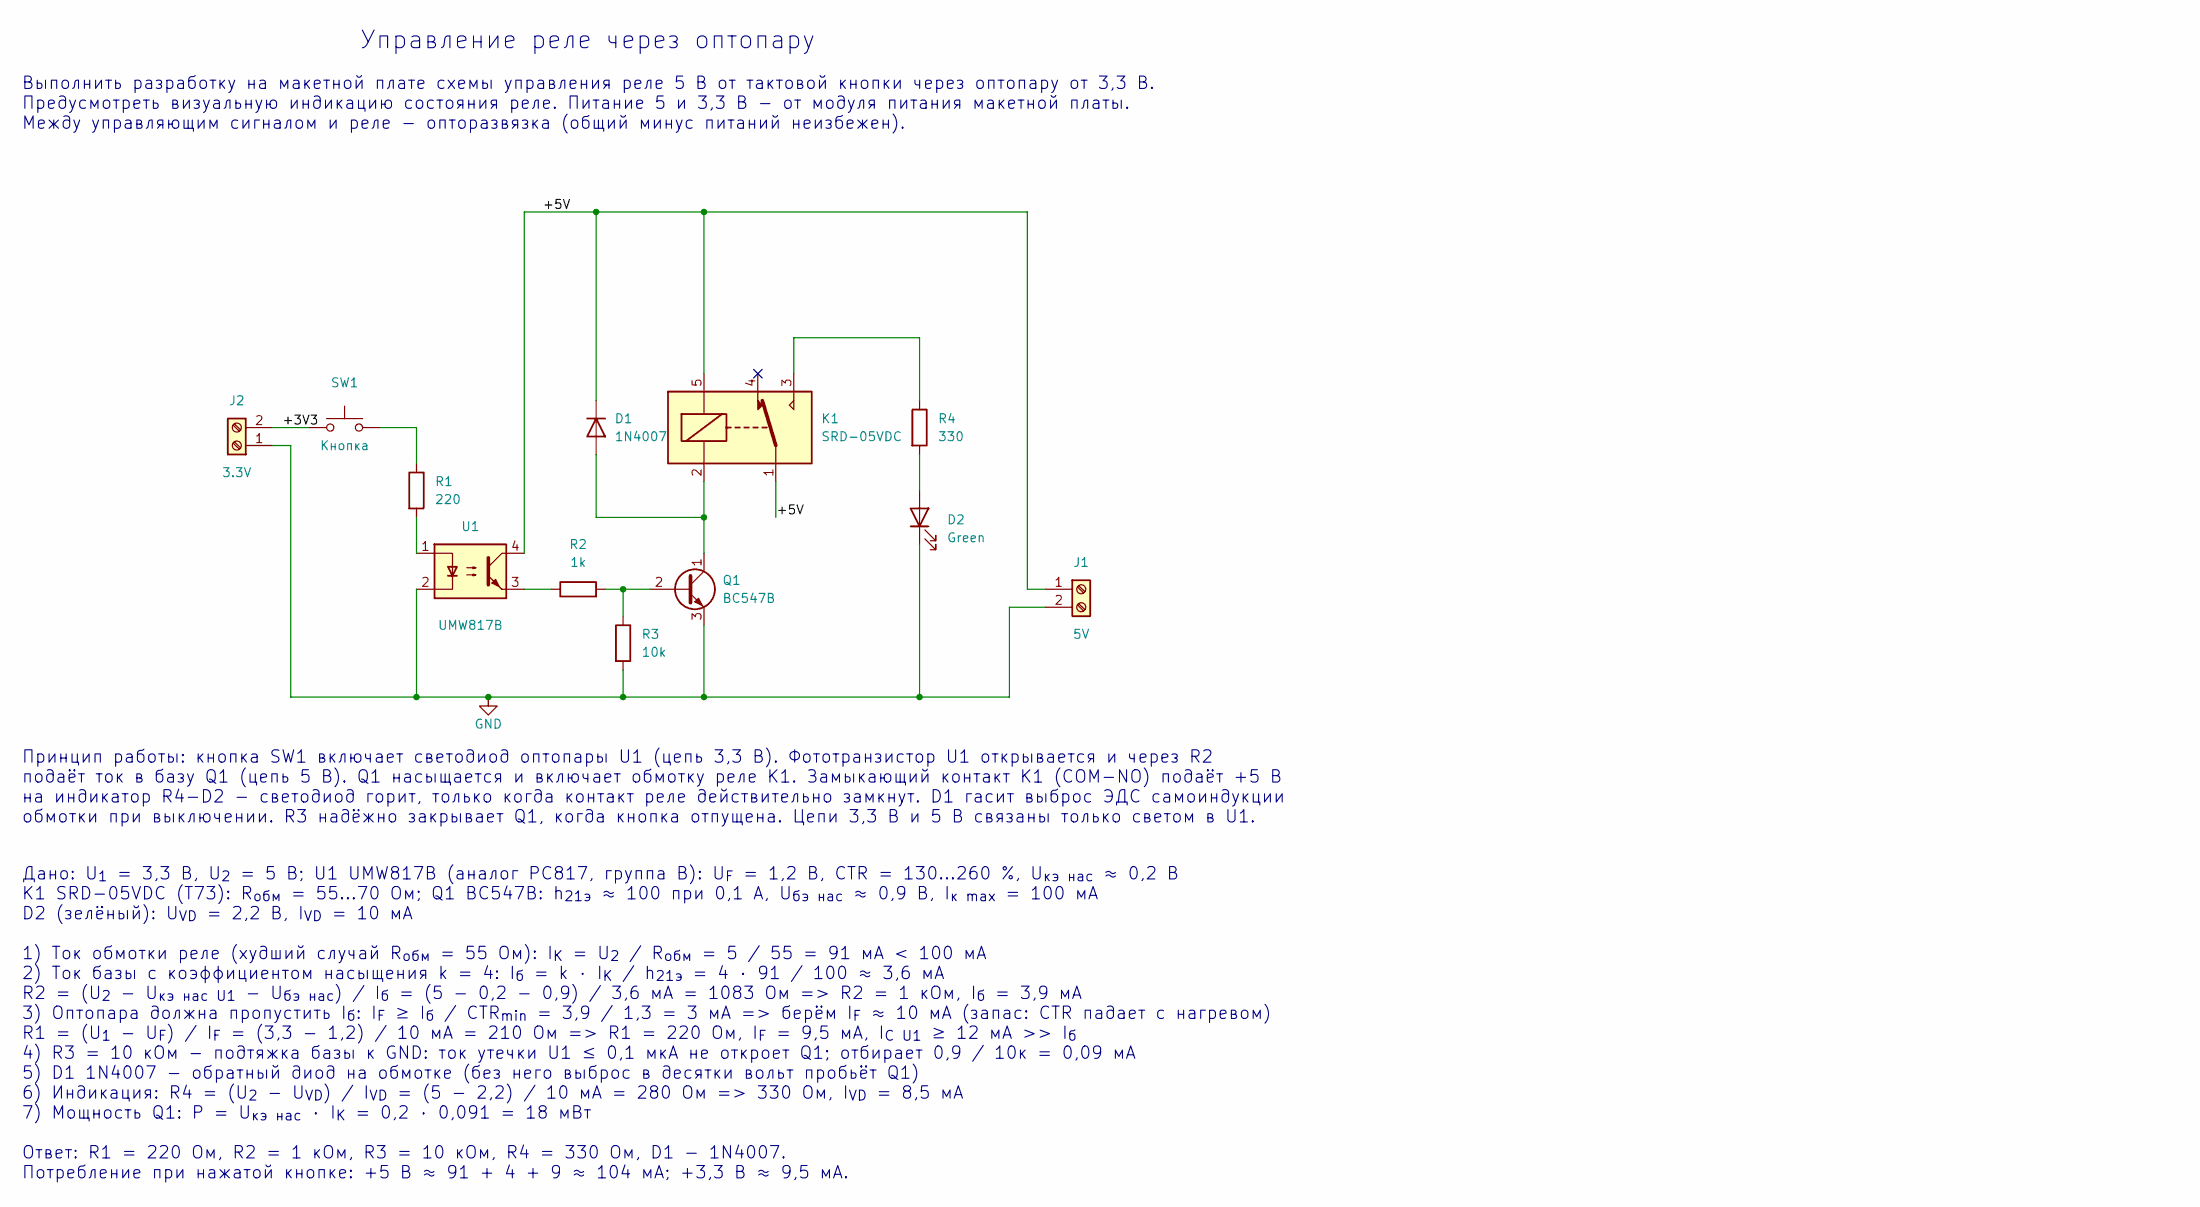
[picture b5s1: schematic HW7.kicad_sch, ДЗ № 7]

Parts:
D1: 1N4007; D_DO-41_SOD81_P10.16mm_Horizontal
D2: Green; LED_D5.0mm
J1: 5V; TerminalBlock_MaiXu_MX126-5.0-02P_1x02_P5.00mm
J2: 3.3V; TerminalBlock_MaiXu_MX126-5.0-02P_1x02_P5.00mm
K1: SRD-05VDC; Relay_SPDT_SANYOU_SRD_Series_Form_C
Q1: BC547B; TO-92L_Inline
R1: 220; R_Axial_DIN0207_L6.3mm_D2.5mm_P10.16mm_Horizontal
R2: 1k; R_Axial_DIN0207_L6.3mm_D2.5mm_P10.16mm_Horizontal
R3: 10k; R_Axial_DIN0207_L6.3mm_D2.5mm_P10.16mm_Horizontal
R4: 330; R_Axial_DIN0207_L6.3mm_D2.5mm_P10.16mm_Horizontal
SW1: Кнопка; SW_PUSH_6mm
U1: UMW817B; DIP-4_W7.62mm

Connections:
+3V3: J2.2, SW1.1
+5V: D1.1 (K), J1.1, K1.1, K1.5, U1.4
BASE: Q1.2 (B), R2.2, R3.1
COIL: D1.2 (A), K1.2, Q1.1 (C)
GND: D2.1 (K), J1.2, J2.1, Q1.3 (E), R3.2, U1.2
LEDIN: R1.2, U1.1
LED_A: D2.2 (A), R4.2
NO: K1.3, R4.1
OPT_E: R2.1, U1.3
SW: R1.1, SW1.2

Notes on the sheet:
Управление реле через оптопару
Выполнить разработку на макетной плате схемы управления реле 5 В от тактовой кнопки через оптопару от 3,3 В. Предусмотреть визуальную индикацию состояния реле. Питание 5 и 3,3 В - от модуля питания макетной платы. Между управляющим сигналом и реле - опторазвязка (общий минус питаний неизбежен).
Принцип работы: кнопка SW1 включает светодиод оптопары U1 (цепь 3,3 В). Фототранзистор U1 открывается и через R2 подаёт ток в базу Q1 (цепь 5 В). Q1 насыщается и включает обмотку реле K1. Замыкающий контакт K1 (COM-NO) подаёт +5 В на индикатор R4-D2 - светодиод горит, только когда контакт реле дейс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
Дано: U_{1} = 3,3 В, U_{2} = 5 В; U1 UMW817B (аналог PC817, группа B): U_{F} = 1,2 В, CTR = 130...260 %, U_{кэ нас} ≈ 0,2 В K1 SRD-05VDC (T73): R_{обм} = 55...70 Ом; Q1 BC547B: h_{21э} ≈ 100 при 0,1 А, U_{бэ нас} ≈ 0,9 В, I_{к max} = 100 мА D2 (зелёный): U_{VD} = 2,2 В, I_{VD} = 10 мА 1) Ток обмотк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
